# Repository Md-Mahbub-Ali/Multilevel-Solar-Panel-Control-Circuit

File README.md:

# Multilevel-Solar-Panel-Control-Circuit
# Just a schematic view of the main control circuit for operating the Time Varying Multilevel Solar Panel Setup.
PCB design will be uploaded later if required.

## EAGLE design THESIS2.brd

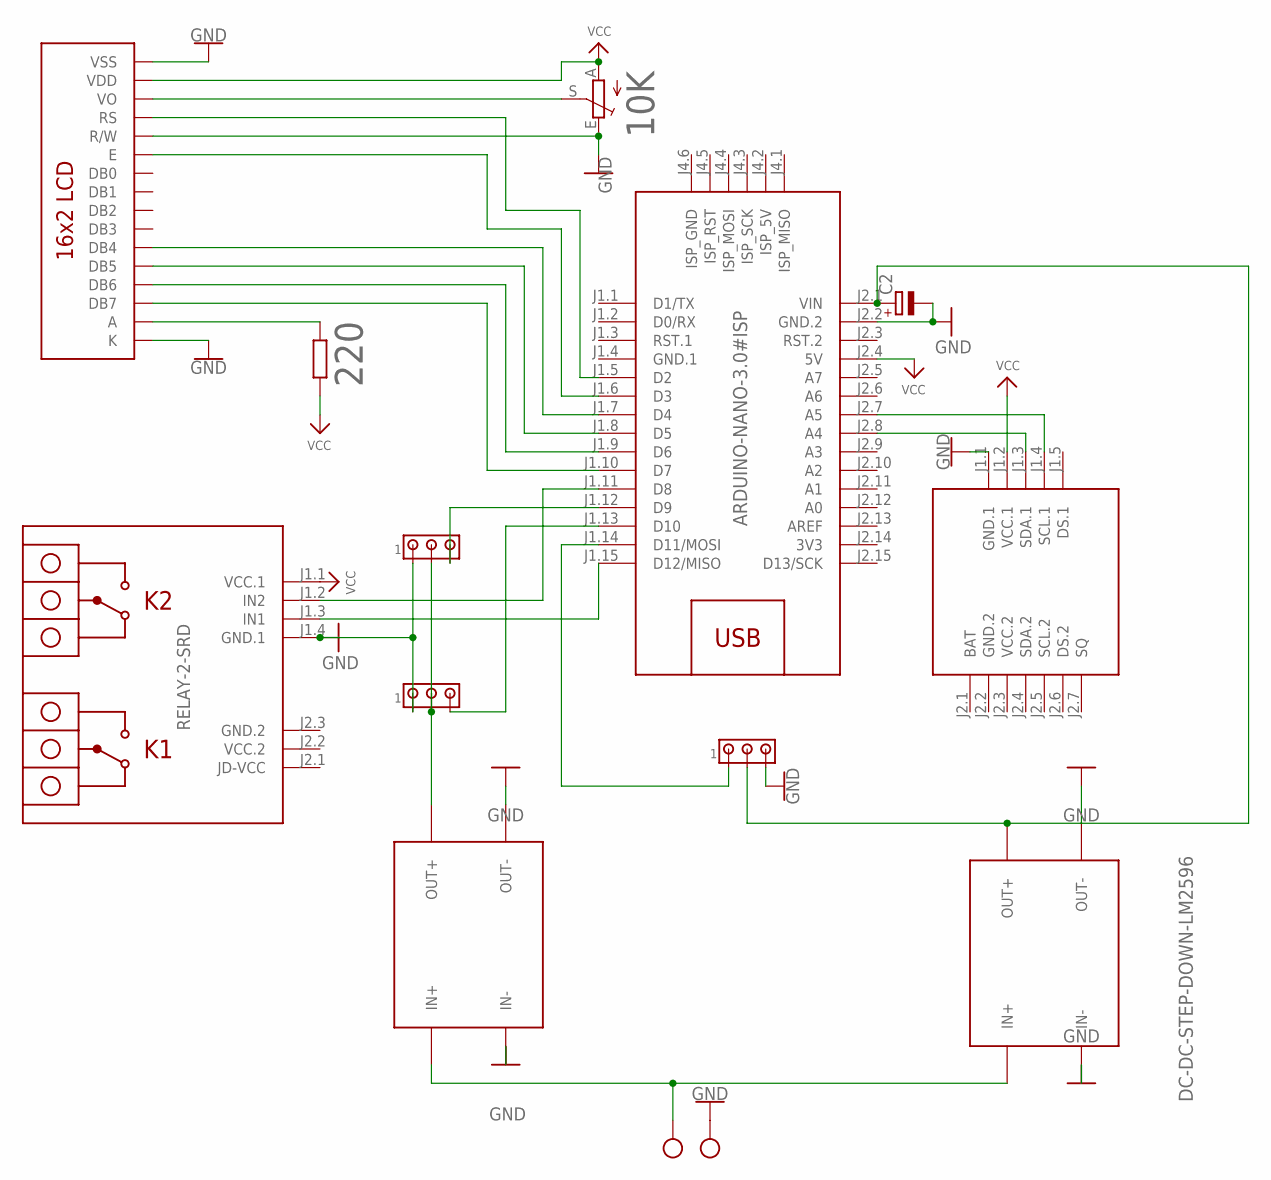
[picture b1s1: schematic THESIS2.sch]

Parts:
C2: CPOL-EUE1.8-4; E1,8-4
J4, J5, J6: MTA03-100; 10X03MTA
LCD1: LCD-16X2NOHOLES; LCD-16X2_NOHOLESNOSILK
M1: ARDUINO-NANO-3.0#ISP
R1: 10K; CIP20C-6MM
R2: 220; 0204/7
U$1: RELAY-2-SRD
U$2, U$3: DC-DC-STEP-DOWN-LM2596
U$5: RTC-EEPROM-BATTERY
X1: AK300/2

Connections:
3V3: M1.J2.14 (3V3)
GND: C2.-, J4.3, J5.1, J6.1, LCD1.1 (VSS), LCD1.5 (R/W), LCD1.16 (K), M1.J2.2 (GND.2), R1.E, U$1.J1.4 (GND.1), U$2.IN-, U$2.OUT-, U$3.IN-, U$3.OUT-, U$5.J1.1 (GND.1), X1.2
GND.1: M1.J1.4 (GND.1)
GND.2: U$1.J2.3 (GND.2), U$5.J2.2 (GND.2)
unnamed: U$2.IN+, U$3.IN+, X1.1
unnamed: LCD1.14 (DB7), M1.J1.10 (D7)
unnamed: LCD1.13 (DB6), M1.J1.9 (D6)
unnamed: LCD1.12 (DB5), M1.J1.8 (D5)
unnamed: LCD1.3 (VO), R1.S
unnamed: LCD1.11 (DB4), M1.J1.7 (D4)
unnamed: LCD1.15 (A), R2.2
unnamed: LCD1.4 (RS), M1.J1.5 (D2)
unnamed: LCD1.6 (E), M1.J1.6 (D3)
unnamed: M1.J2.8 (A4), U$5.J1.3 (SDA.1)
unnamed: M1.J2.7 (A5), U$5.J1.4 (SCL.1)
unnamed: J4.1, M1.J1.14 (D11/MOSI)
unnamed: C2.+, J4.2, M1.J2.1 (VIN), U$3.OUT+
unnamed: J5.2, J6.2, U$2.OUT+
unnamed: J6.3, M1.J1.12 (D9)
unnamed: M1.J1.15 (D12/MISO), U$1.J1.3 (IN1)
unnamed: M1.J1.11 (D8), U$1.J1.2 (IN2)
unnamed: J5.3, M1.J1.13 (D10)
VCC: LCD1.2 (VDD), M1.J2.4 (5V), R1.A, R2.1, U$1.J1.1 (VCC.1), U$5.J1.2 (VCC.1)
VCC.2: U$1.J2.2 (VCC.2), U$5.J2.3 (VCC.2)

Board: 2 copper layers, 13 parts (0 on the bottom side), 22 nets, no tracks yet.

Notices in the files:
parts and their libraries:
SparkFun-Displays: Licensing: Creative Commons ShareAlike 4.0 International - https://creativecommons.org/licenses/by-sa/4.0
diy-modules step down: Released under the Creative Commons Attribution 4.0 International License: http://creativecommons.org/licenses/by/4.0
